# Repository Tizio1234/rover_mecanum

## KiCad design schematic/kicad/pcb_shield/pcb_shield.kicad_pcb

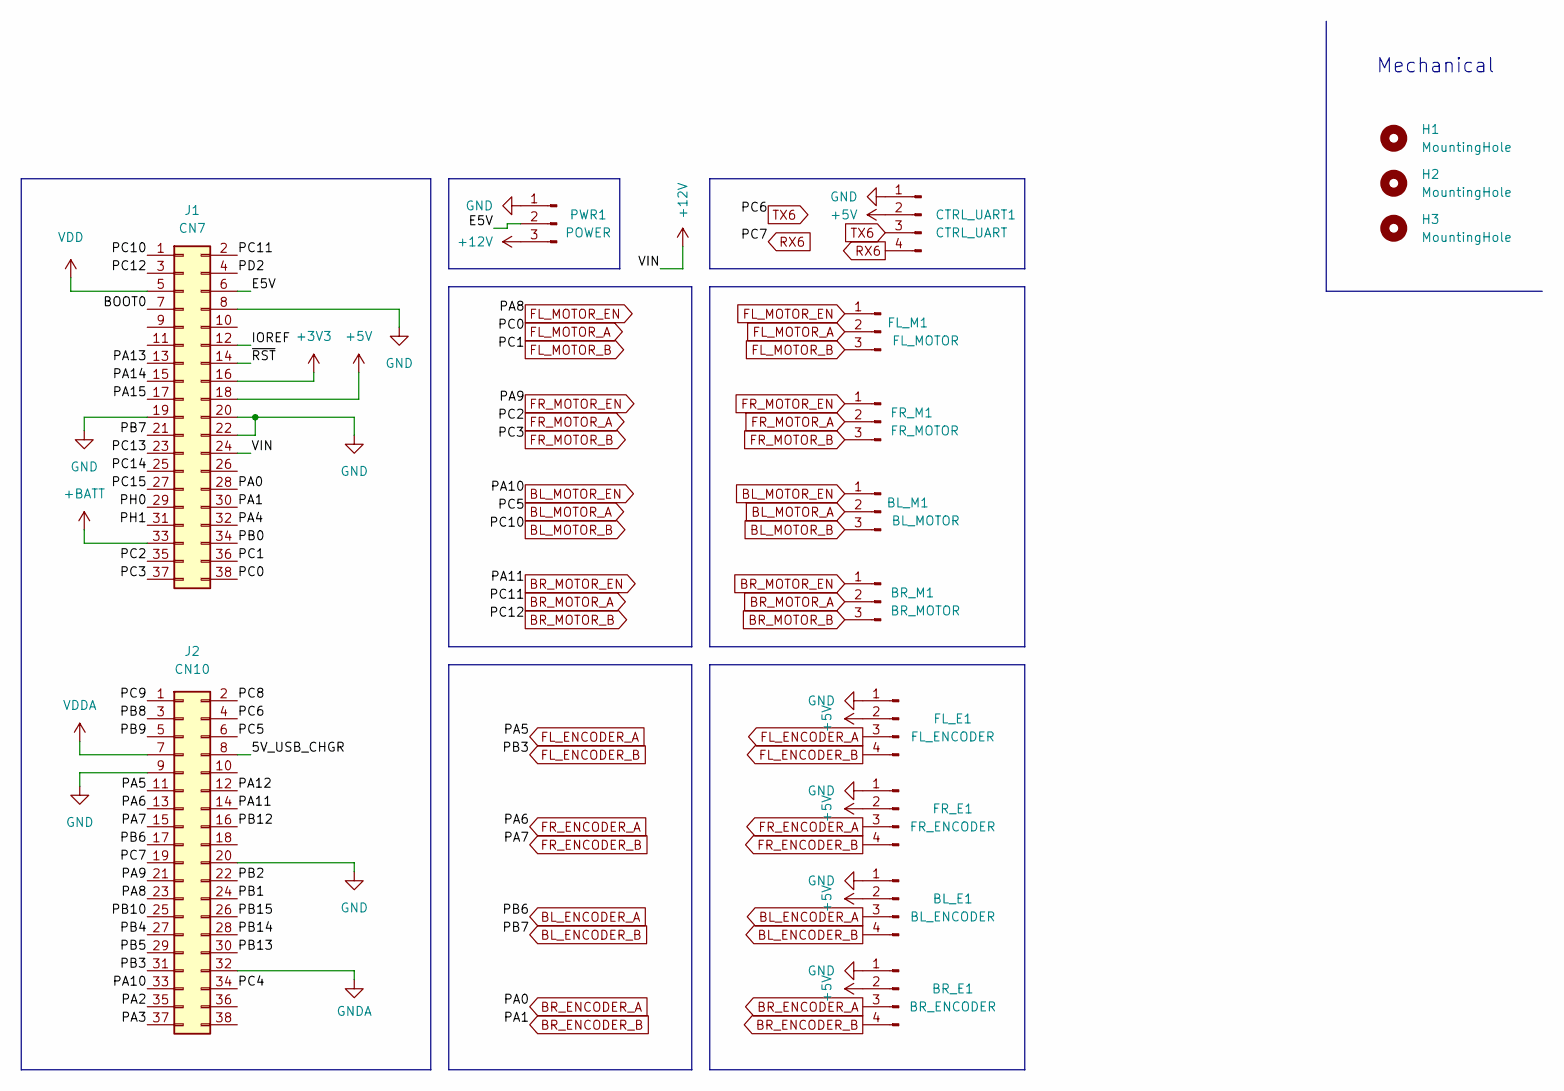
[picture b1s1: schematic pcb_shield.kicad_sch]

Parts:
BL_E1: BL_ENCODER; PinHeader_1x04_P2.54mm_Vertical
BL_M1: BL_MOTOR; PinHeader_1x03_P2.54mm_Vertical
BR_E1: BR_ENCODER; PinHeader_1x04_P2.54mm_Vertical
BR_M1: BR_MOTOR; PinHeader_1x03_P2.54mm_Vertical
CTRL_UART1: CTRL_UART; PinHeader_1x04_P2.54mm_Vertical
FL_E1: FL_ENCODER; PinHeader_1x04_P2.54mm_Vertical
FL_M1: FL_MOTOR; PinHeader_1x03_P2.54mm_Vertical
FR_E1: FR_ENCODER; PinHeader_1x04_P2.54mm_Vertical
FR_M1: FR_MOTOR; PinHeader_1x03_P2.54mm_Vertical
H1, H2, H3: MountingHole; MountingHole_3.2mm_M3
J1: CN7; PinSocket_2x19_P2.54mm_Vertical
J2: CN10; PinSocket_2x19_P2.54mm_Vertical
PWR1: POWER; PinHeader_1x03_P2.54mm_Vertical

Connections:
+3V3: J1.16
+5V: BL_E1.2, BR_E1.2, CTRL_UART1.2, FL_E1.2, FR_E1.2, J1.18
+12V: J1.24, PWR1.3
+BATT: J1.33
/5V_USB_CHGR: J2.8
/BOOT0: J1.7
/E5V: J1.6, PWR1.2
/IOREF: J1.12
/PA2: J2.35
/PA3: J2.37
/PA4: J1.32
/PA12: J2.12
/PA13: J1.13
/PA14: J1.15
/PA15: J1.17
/PB0: J1.34
/PB1: J2.24
/PB2: J2.22
/PB4: J2.27
/PB5: J2.29
/PB8: J2.3
/PB9: J2.5
/PB10: J2.25
/PB12: J2.16
/PB13: J2.30
/PB14: J2.28
/PB15: J2.26
/PC4: J2.34
/PC8: J2.2
/PC9: J2.1
/PC13: J1.23
/PC14: J1.25
/PC15: J1.27
/PD2: J1.4
/PH0: J1.29
/PH1: J1.31
/~RST: J1.14
BL_ENCODER_A: BL_E1.3, J2.17
BL_ENCODER_B: BL_E1.4, J1.21
BL_MOTOR_A: BL_M1.2, J2.6
BL_MOTOR_B: BL_M1.3, J1.1
BL_MOTOR_EN: BL_M1.1, J2.33
BR_ENCODER_A: BR_E1.3, J1.28
BR_ENCODER_B: BR_E1.4, J1.30
BR_MOTOR_A: BR_M1.2, J1.2
BR_MOTOR_B: BR_M1.3, J1.3
BR_MOTOR_EN: BR_M1.1, J2.14
FL_ENCODER_A: FL_E1.3, J2.11
FL_ENCODER_B: FL_E1.4, J2.31
FL_MOTOR_A: FL_M1.2, J1.38
FL_MOTOR_B: FL_M1.3, J1.36
FL_MOTOR_EN: FL_M1.1, J2.23
FR_ENCODER_A: FR_E1.3, J2.13
FR_ENCODER_B: FR_E1.4, J2.15
FR_MOTOR_A: FR_M1.2, J1.35
FR_MOTOR_B: FR_M1.3, J1.37
FR_MOTOR_EN: FR_M1.1, J2.21
GND: BL_E1.1, BR_E1.1, CTRL_UART1.1, FL_E1.1, FR_E1.1, J1.8, J1.19, J1.20, J1.22, J2.9, J2.20, PWR1.1
GNDA: J2.32
RX6: CTRL_UART1.4, J2.19
TX6: CTRL_UART1.3, J2.4
VDD: J1.5
VDDA: J2.7

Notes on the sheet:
Mechanical

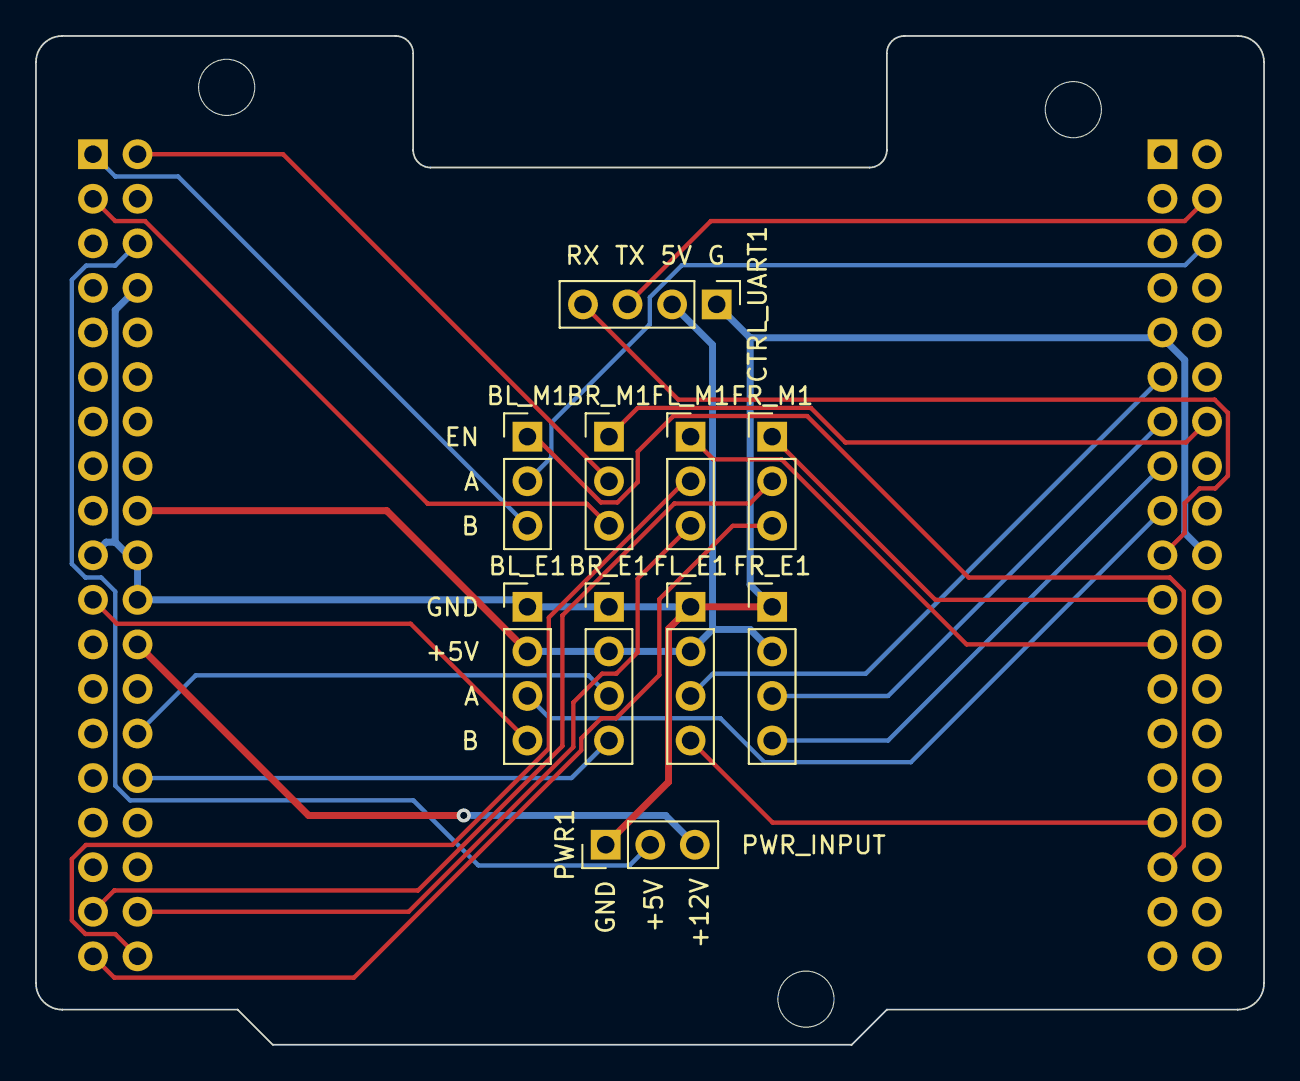
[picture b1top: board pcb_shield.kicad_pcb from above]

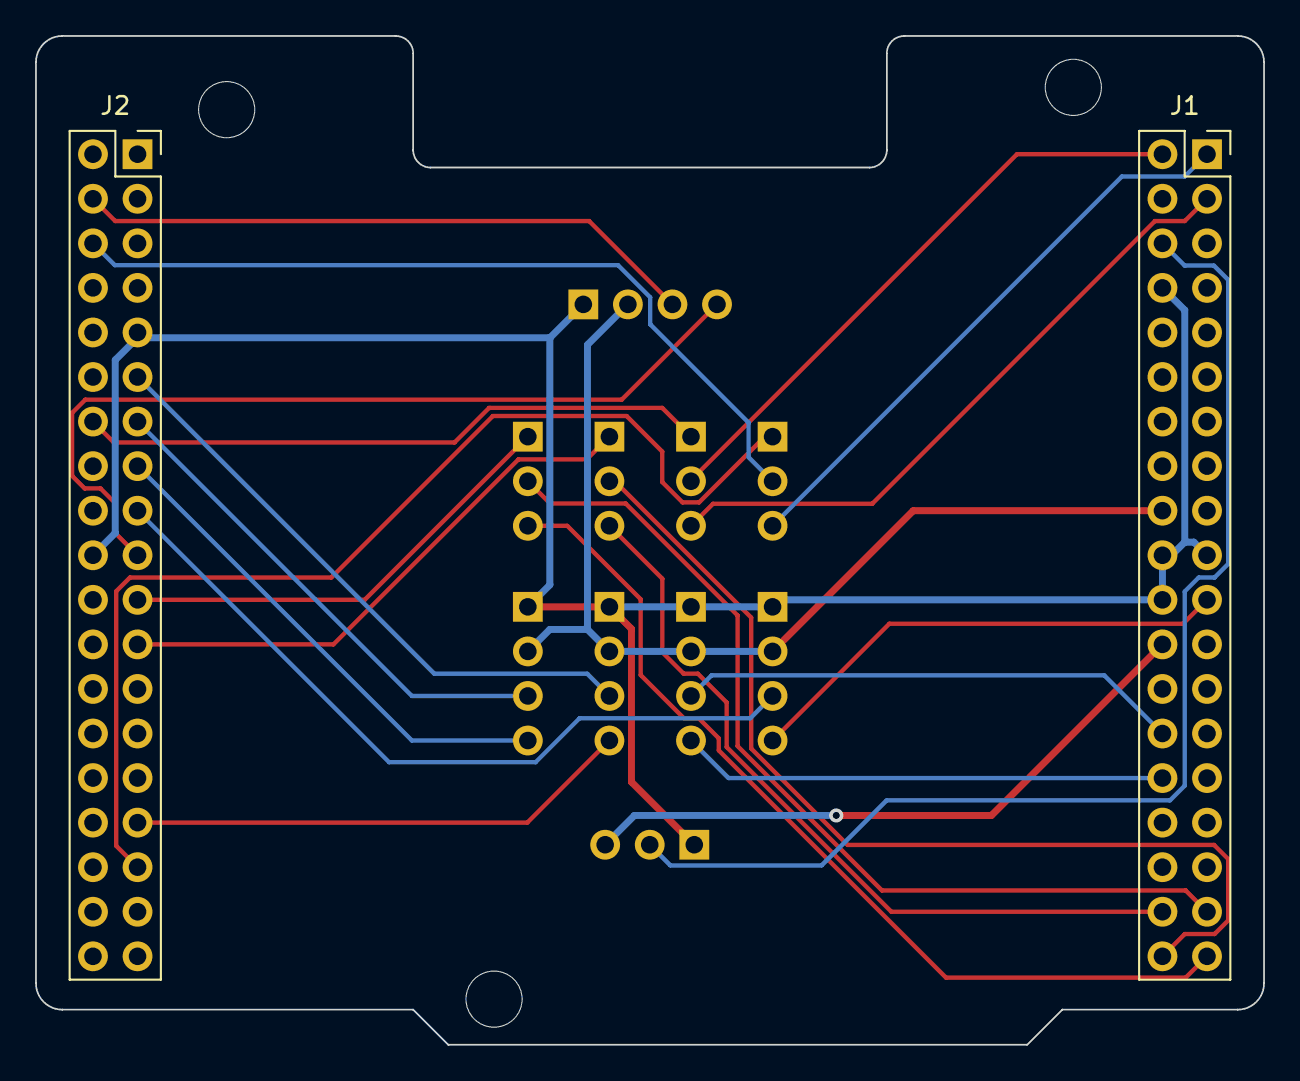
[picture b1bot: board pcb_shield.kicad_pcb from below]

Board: 2 copper layers, 70.0 x 57.5 mm, 15 parts (2 on the bottom side), 26 nets.

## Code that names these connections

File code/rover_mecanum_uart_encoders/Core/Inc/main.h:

/* USER CODE BEGIN Header */
/**
  ******************************************************************************
  * @file           : main.h
  * @brief          : Header for main.c file.
  *                   This file contains the common defines of the application.
  ******************************************************************************
  * @attention
  *
  * Copyright (c) 2024 STMicroelectronics.
  * All rights reserved.
  *
  * This software is licensed under terms that can be found in the LICENSE file
  * in the root directory of this software component.
  * If no LICENSE file comes with this software, it is provided AS-IS.
  *
  ******************************************************************************
  */
/* USER CODE END Header */

/* Define to prevent recursive inclusion -------------------------------------*/
#ifndef __MAIN_H
#define __MAIN_H

#ifdef __cplusplus
extern "C" {
#endif

/* Includes ------------------------------------------------------------------*/
#include "stm32f4xx_hal.h"

/* Private includes ----------------------------------------------------------*/
/* USER CODE BEGIN Includes */

/* USER CODE END Includes */

/* Exported types ------------------------------------------------------------*/
/* USER CODE BEGIN ET */

/* USER CODE END ET */

/* Exported constants --------------------------------------------------------*/
/* USER CODE BEGIN EC */

/* USER CODE END EC */

/* Exported macro ------------------------------------------------------------*/
/* USER CODE BEGIN EM */

/* USER CODE END EM */

void HAL_TIM_MspPostInit(TIM_HandleTypeDef *htim);

/* Exported functions prototypes ---------------------------------------------*/
void Error_Handler(void);

/* USER CODE BEGIN EFP */

/* USER CODE END EFP */

/* Private defines -----------------------------------------------------------*/
#define B1_Pin GPIO_PIN_13
#define B1_GPIO_Port GPIOC
#define B1_EXTI_IRQn EXTI15_10_IRQn
#define BR_ENCODER_A_Pin GPIO_PIN_0
#define BR_ENCODER_A_GPIO_Port GPIOA
#define BR_ENCODER_B_Pin GPIO_PIN_1
#define BR_ENCODER_B_GPIO_Port GPIOA
#define FL_ENCODER_A_Pin GPIO_PIN_5
#define FL_ENCODER_A_GPIO_Port GPIOA
#define FL_MOTOR_A_Pin GPIO_PIN_4
#define FL_MOTOR_A_GPIO_Port GPIOC
#define BR_MOTOR_B_Pin GPIO_PIN_5
#define BR_MOTOR_B_GPIO_Port GPIOC
#define BL_MOTOR_A_Pin GPIO_PIN_1
#define BL_MOTOR_A_GPIO_Port GPIOB
#define BL_MOTOR_B_Pin GPIO_PIN_2
#define BL_MOTOR_B_GPIO_Port GPIOB
#define BR_MOTOR_A_Pin GPIO_PIN_12
#define BR_MOTOR_A_GPIO_Port GPIOB
#define FL_MOTOR_B_Pin GPIO_PIN_13
#define FL_MOTOR_B_GPIO_Port GPIOB
#define FR_MOTOR_A_Pin GPIO_PIN_14
#define FR_MOTOR_A_GPIO_Port GPIOB
#define FR_MOTOR_B_Pin GPIO_PIN_15
#define FR_MOTOR_B_GPIO_Port GPIOB
#define FR_ENCODER_B_Pin GPIO_PIN_7
#define FR_ENCODER_B_GPIO_Port GPIOC
#define FL_MOTOR_EN_Pin GPIO_PIN_8
#define FL_MOTOR_EN_GPIO_Port GPIOA
#define FR_MOTOR_EN_Pin GPIO_PIN_9
#define FR_MOTOR_EN_GPIO_Port GPIOA
#define BL_MOTOR_EN_Pin GPIO_PIN_10
#define BL_MOTOR_EN_GPIO_Port GPIOA
#define BR_MOTOR_EN_Pin GPIO_PIN_11
#define BR_MOTOR_EN_GPIO_Port GPIOA
#define TMS_Pin GPIO_PIN_13
#define TMS_GPIO_Port GPIOA
#define TCK_Pin GPIO_PIN_14
#define TCK_GPIO_Port GPIOA
#define FL_ENCODER_B_Pin GPIO_PIN_3
#define FL_ENCODER_B_GPIO_Port GPIOB
#define FR_ENCODER_A_Pin GPIO_PIN_4
#define FR_ENCODER_A_GPIO_Port GPIOB
#define BL_ENCODER_A_Pin GPIO_PIN_6
#define BL_ENCODER_A_GPIO_Port GPIOB
#define BL_ENCODER_B_Pin GPIO_PIN_7
#define BL_ENCODER_B_GPIO_Port GPIOB

/* USER CODE BEGIN Private defines */

/* USER CODE END Private defines */

#ifdef __cplusplus
}
#endif

#endif /* __MAIN_H */

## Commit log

2024-05-10 gpio conf description
2024-05-11 pcb schematic
2024-05-12 progress with code and pcb shield
2024-05-13 change shield template1
2024-05-13 first working versio
2024-05-13 first actual working version
2024-05-15 fix power input connector
2024-05-19 using cmake fetch content to reduce project size and for better dependencies management
2024-05-19 small modification
2024-05-19 kicad pcb shield schematic gitignore to remove backups(git version control is enough)
2024-05-20 gerber files
2024-05-20 start of uart comm, todo: understand why stm32cubemx gets recompiled for every target that needs it
2024-05-26 uart rb progress
2024-05-27 event fun is called from isr, to reduce memory usage, user must send received packets with a queue
2024-05-27 fix lwpkt processing
2024-05-27 remove unused code
2024-06-02 work in progress
2024-06-04 progress for robot lib
2024-06-05 first version of robot library
2024-06-05 Functioning version
2024-07-02 newer uart rb version
2024-07-02 better cmake and project structure
2024-07-02 smal changes
2024-10-27 removed unnecessary stuff, better gitignore
2024-10-27 rust base version
2024-10-27 important fix for flashing issues
2024-10-27 removed unnecessary stuff
2024-10-27 separate lib and bin crates
2024-10-31 working wrapper to split Pwm trait into multiple PwmPin and SetDutyCycle objects, using RefCell. Project structure is still in very early stages.
2024-10-31 better direction setting and a few tests
2024-11-01 better project structure, making use of cargo workspaces
2024-11-01 new rover lib structure(probably better)
2024-11-01 new type for power, four wheel robot trait, mecanum robot trait and implementation for four wheel robot
2024-11-02 new generics and better everything(sorry in advance for the short commit message)
2024-11-02 pcb maintenance: no connect, updated erc, fix a few erc warnings/errors
2024-11-03 first kind of working version
2024-11-04 fix channel selection(the same channel was used for 3 motors) and a few touches
2024-11-04 pin selection for old circuit, feature behavioyut to be done to allow compilation for different schematics(old circuit and pcb shield)
2024-11-07 decoding cobs messages and printing json results, logging framework to be revised to log objects that do not support defmt
2024-11-08 tested version sending commands from pc
2024-11-12 new lib types, BSP configuration for old circuit and new pcb, safety turn off
2024-11-12 fixed safety timer
2024-11-17 working version, tested with serial adapter from PC
2024-12-06 remove trailing character
2024-12-06 better logging, now values are printed with debug
2024-12-06 stable instead of 1.82
2025-01-12 message parsing is now done with a strongly typed structure, also safety timer works, as of now is is 500ms
2025-02-09 Update LICENSE
